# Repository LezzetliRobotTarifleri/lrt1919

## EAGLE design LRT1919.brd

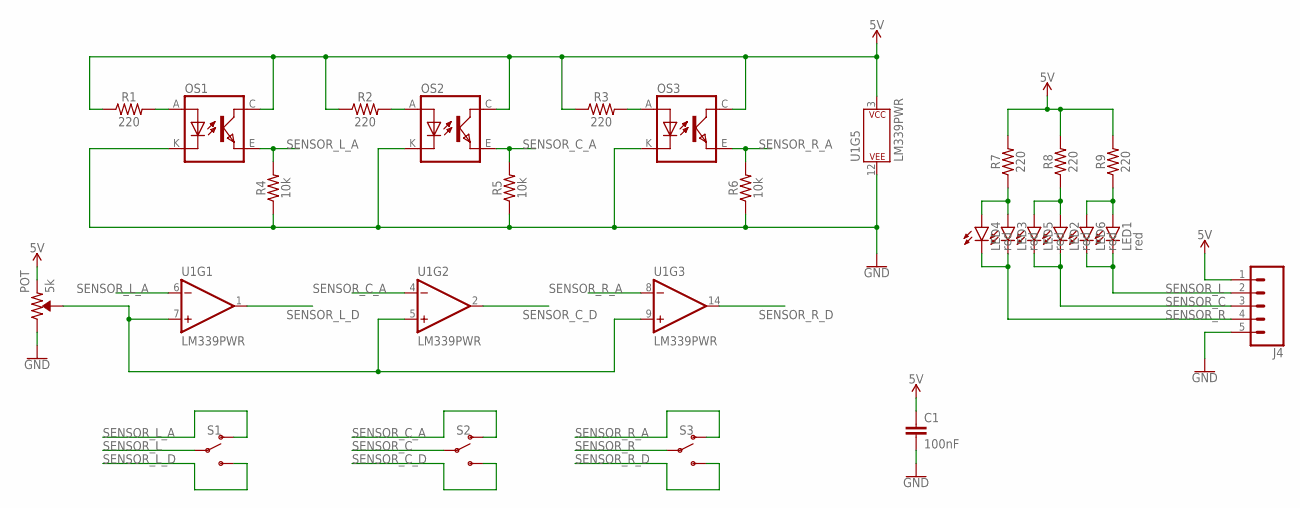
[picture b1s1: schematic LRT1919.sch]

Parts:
C1: 100nF; 0805
J4: CONN_05; 1X05
LED1, LED2, LED3, LED4, LED5, LED6: red; SML0805
OS1, OS2, OS3: TCRT5000
POT: 5k; TRIMPOT-SMD-5MM
R1, R2, R3, R7, R8, R9: 220; 0805
R4, R5, R6: 10k; 0805
S1, S2, S3: SWITCH-SPDT-SMD-RIGHT-ANGLE; SWITCH_SPST_SMD_A
U1: LM339PWR; TSSOP-14

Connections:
5V: C1.1, J4.1, OS1.C (COLLECTOR), OS2.C (COLLECTOR), OS3.C (COLLECTOR), POT.A (CCW), R1.1, R2.1, R3.1, R7.2, R8.2, R9.2, U1.3 (P$V+)
GND: C1.2, J4.5, OS1.K (CATHODE), OS2.K (CATHODE), OS3.K (CATHODE), POT.C (CW), R4.1, R5.1, R6.1, U1.12 (P$V-)
unnamed: OS1.A (ANODE), R1.2
unnamed: OS2.A (ANODE), R2.2
unnamed: OS3.A (ANODE), R3.2
unnamed: LED3.A, LED4.A, R7.1
unnamed: LED2.A, LED5.A, R8.1
unnamed: POT.B (WIPER), U1.5 (+IN), U1.7 (+IN), U1.9 (+IN)
unnamed: LED1.A, LED6.A, R9.1
SENSOR_C: J4.3, LED2.C, LED5.C, S2.2
SENSOR_C_A: OS2.E (EMITTER), R5.2, S2.1 (O), U1.4 (-IN)
SENSOR_C_D: S2.3 (S), U1.2 (OUT)
SENSOR_L: J4.2, LED1.C, LED6.C, S1.2
SENSOR_L_A: OS1.E (EMITTER), R4.2, S1.1 (O), U1.6 (-IN)
SENSOR_L_D: S1.3 (S), U1.1 (OUT)
SENSOR_R: J4.4, LED3.C, LED4.C, S3.2
SENSOR_R_A: OS3.E (EMITTER), R6.2, S3.1 (O), U1.8 (-IN)
SENSOR_R_D: S3.3 (S), U1.14 (OUT)

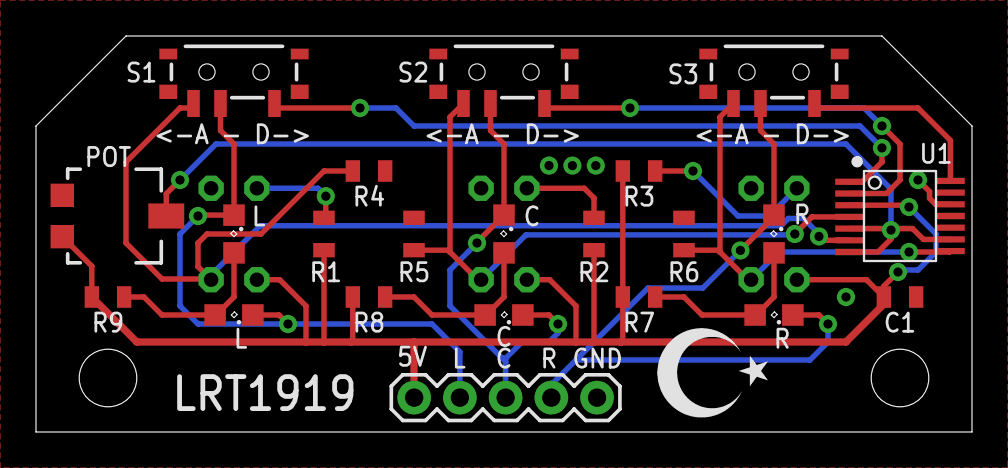
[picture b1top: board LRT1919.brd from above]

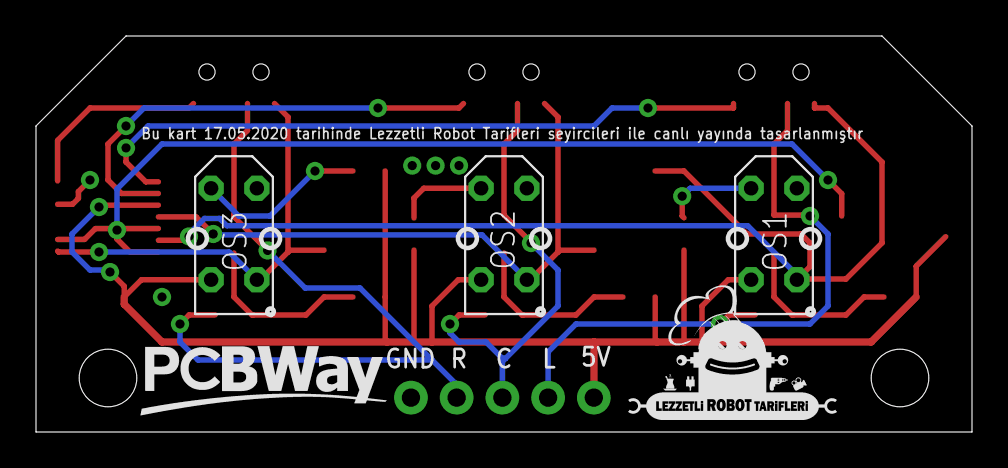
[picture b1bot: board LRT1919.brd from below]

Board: 2 copper layers, 52.0 x 22.0 mm, 28 parts (5 on the bottom side), 18 nets.

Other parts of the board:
U$2: LOGO0.001
U$3: PCBWAY_LOGO_0.01
U$5: TR_MINI

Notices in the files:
parts and their libraries:
SparkFun-Resistors: Licensing: Creative Commons ShareAlike 4.0 International - https://creativecommons.org/licenses/by-sa/4.0
